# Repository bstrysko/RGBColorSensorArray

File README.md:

RGBColorSensorArray
===================

RGB Color Sensor Array Schematics and Source Code

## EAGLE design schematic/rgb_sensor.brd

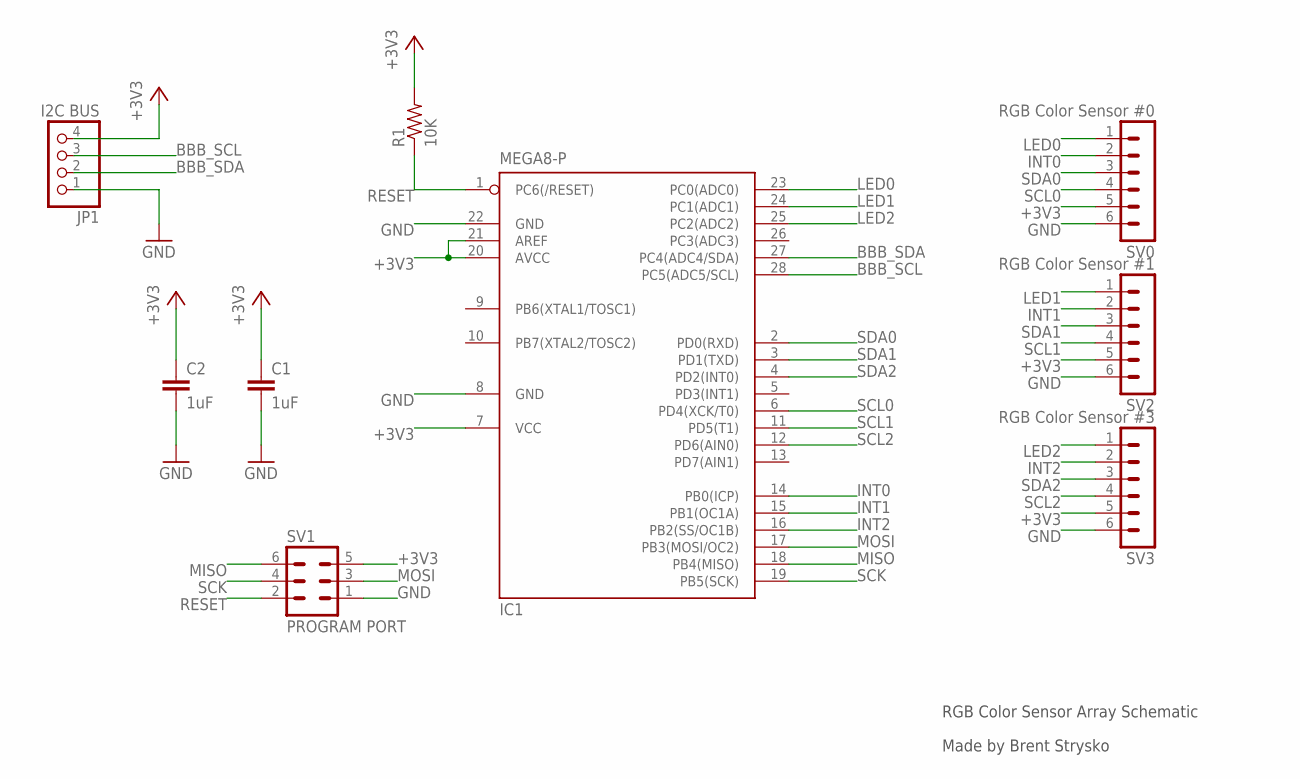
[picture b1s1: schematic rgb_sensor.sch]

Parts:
C1, C2: 1uF; CAP-PTH-SMALL-KIT
IC1: MEGA8-P; DIL28-3
JP1: I2C BUS; 1X04
R1: 10K; AXIAL-0.4
SV0: RGB Color Sensor #0; MA06-1
SV1: PROGRAM PORT; MA03-2
SV2: RGB Color Sensor #1; MA06-1
SV3: RGB Color Sensor #3; MA06-1

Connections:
+3V3: C1.1, C2.1, IC1.7 (VCC), IC1.20 (AVCC), IC1.21 (AREF), JP1.4, R1.P$2 (2), SV0.5, SV1.5, SV2.5, SV3.5
BBB_SCL: IC1.28 (PC5(ADC5/SCL)), JP1.3
BBB_SDA: IC1.27 (PC4(ADC4/SDA)), JP1.2
GND: C1.2, C2.2, IC1.8 (GND), IC1.22 (GND), JP1.1, SV0.6, SV1.1, SV2.6, SV3.6
INT0: IC1.14 (PB0(ICP)), SV0.2
INT1: IC1.15 (PB1(OC1A)), SV2.2
INT2: IC1.16 (PB2(SS/OC1B)), SV3.2
LED0: IC1.23 (PC0(ADC0)), SV0.1
LED1: IC1.24 (PC1(ADC1)), SV2.1
LED2: IC1.25 (PC2(ADC2)), SV3.1
MISO: IC1.18 (PB4(MISO)), SV1.6
MOSI: IC1.17 (PB3(MOSI/OC2)), SV1.3
RESET: IC1.1 (PC6(/RESET)), R1.P$1 (1), SV1.2
SCK: IC1.19 (PB5(SCK)), SV1.4
SCL0: IC1.6 (PD4(XCK/T0)), SV0.4
SCL1: IC1.11 (PD5(T1)), SV2.4
SCL2: IC1.12 (PD6(AIN0)), SV3.4
SDA0: IC1.2 (PD0(RXD)), SV0.3
SDA1: IC1.3 (PD1(TXD)), SV2.3
SDA2: IC1.4 (PD2(INT0)), SV3.3

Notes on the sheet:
RGB Color Sensor Array Schematic
Made by Brent Strysko

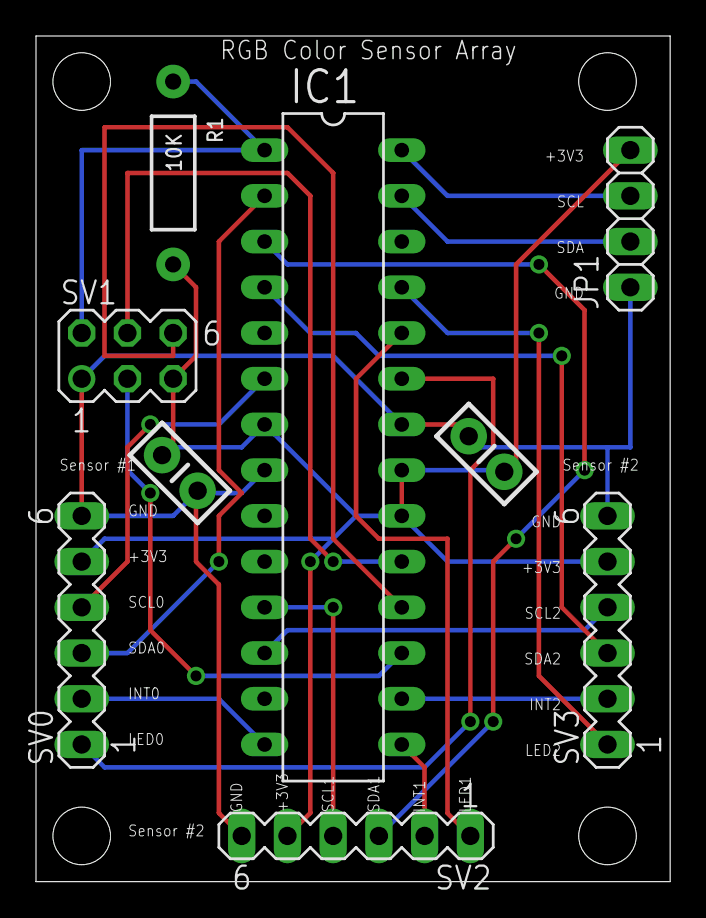
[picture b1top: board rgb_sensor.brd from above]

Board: 2 copper layers, 35.2 x 47.0 mm, 9 parts (0 on the bottom side), 20 nets.

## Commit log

2014-01-31 Able to detect defects fast
2014-02-06 I2C Master library to communicate with RGBColorSensorArray and test program. Still need to implement firmware
2014-02-06 Basic control over LEDS with on, off, and blink functionality. Bug where only first LED can properly be written to
2014-02-07 Fixed LED bug by placing RGBSensor global structs in SRAM and moving stack forward as heap data is currently not supported since bootloader buffer lives there
2014-03-19 Basic library implemented for I2C bit banging. Still need to test
2014-03-25 Original schematic and board design
2014-03-25 Redesigned schematic and board. Added decoupling capacitors, pullup resistor on reset, and shrunk board size
2014-03-25 Improved minor bugs in I2C code. Still need to figure out cause of non-working bus with logic analyzer
2014-03-25 Fixed I2C low level bugs. Can now read RGB Color Sensor Device IDs.
2014-03-26 Refactored SI2CMaster code. Able to read from 3x RGB Color Sensors.
2014-03-26 Now print out status of Color Sensors in a row as opposed to clearing the screen
2014-04-14 New communication protocol such that defect detection is done outside the library and CRGB are transmitted to the I2C master
2014-04-17 Moved calibration code to main class

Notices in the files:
parts and their libraries:
SparkFun-Passives: Licensing: CC v3.0 Share-Alike You are welcome to use this library for commercial purposes.
